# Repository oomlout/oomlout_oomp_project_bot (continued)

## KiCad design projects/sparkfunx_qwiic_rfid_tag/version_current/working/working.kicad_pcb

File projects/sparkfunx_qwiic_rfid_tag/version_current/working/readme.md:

# OOMP Project  
## Qwiic_RFID_Tag  by sparkfunX  
  
oomp key: oomp_projects_flat_sparkfunx_qwiic_rfid_tag  
(snippet of original readme)  
  
- SparkX ST25DV64KC Dynamic NFC/RFID Tag  
  
<p align="center">  
      
    <a href="https://twitter.com/intent/follow?screen_name=sparkfun">  
                    </a>  
</p>  
  
<table class="table table-hover table-striped table-bordered">  
    <tr align="center">  
     <td></td>  
    </tr>  
    <tr align="center">  
        <td><a href="https://www.sparkfun.com/products/19035">SparkFun Qwiic Dynamic RFID Tag - ST25DV64KC (SPX-19035)</a></td>  
    </tr>  
</table>  
  
The STMicroelectronics ST25DV _**dynamic**_ Near Frequency Communication / Radio Frequency Identification tag ICs are awesome! The ST25DV64KC offers 64-kBit (8-kBytes) of EEPROM memory which can be accessed over both I2C and RF (NFC)! It's a state-of-the-art tag which conforms to ISO/IEC 15693 or NFC Forum Type 5 recommendations. You can read and write the tag's memory using NFC even while the tag is powered down or disconnected!  
  
The EEPROM memory can be divided into four areas, each of which can have different levels of protection applied. Want to store your data so everyone has read and write acc  
  full source readme at [readme_src.md](readme_src.md)  
  
source repo at: [https://github.com/sparkfunX/Qwiic_RFID_Tag](https://github.com/sparkfunX/Qwiic_RFID_Tag)  
## Board  

## Schematic  

[schematic pdf](working_schematic.pdf)  
## Images

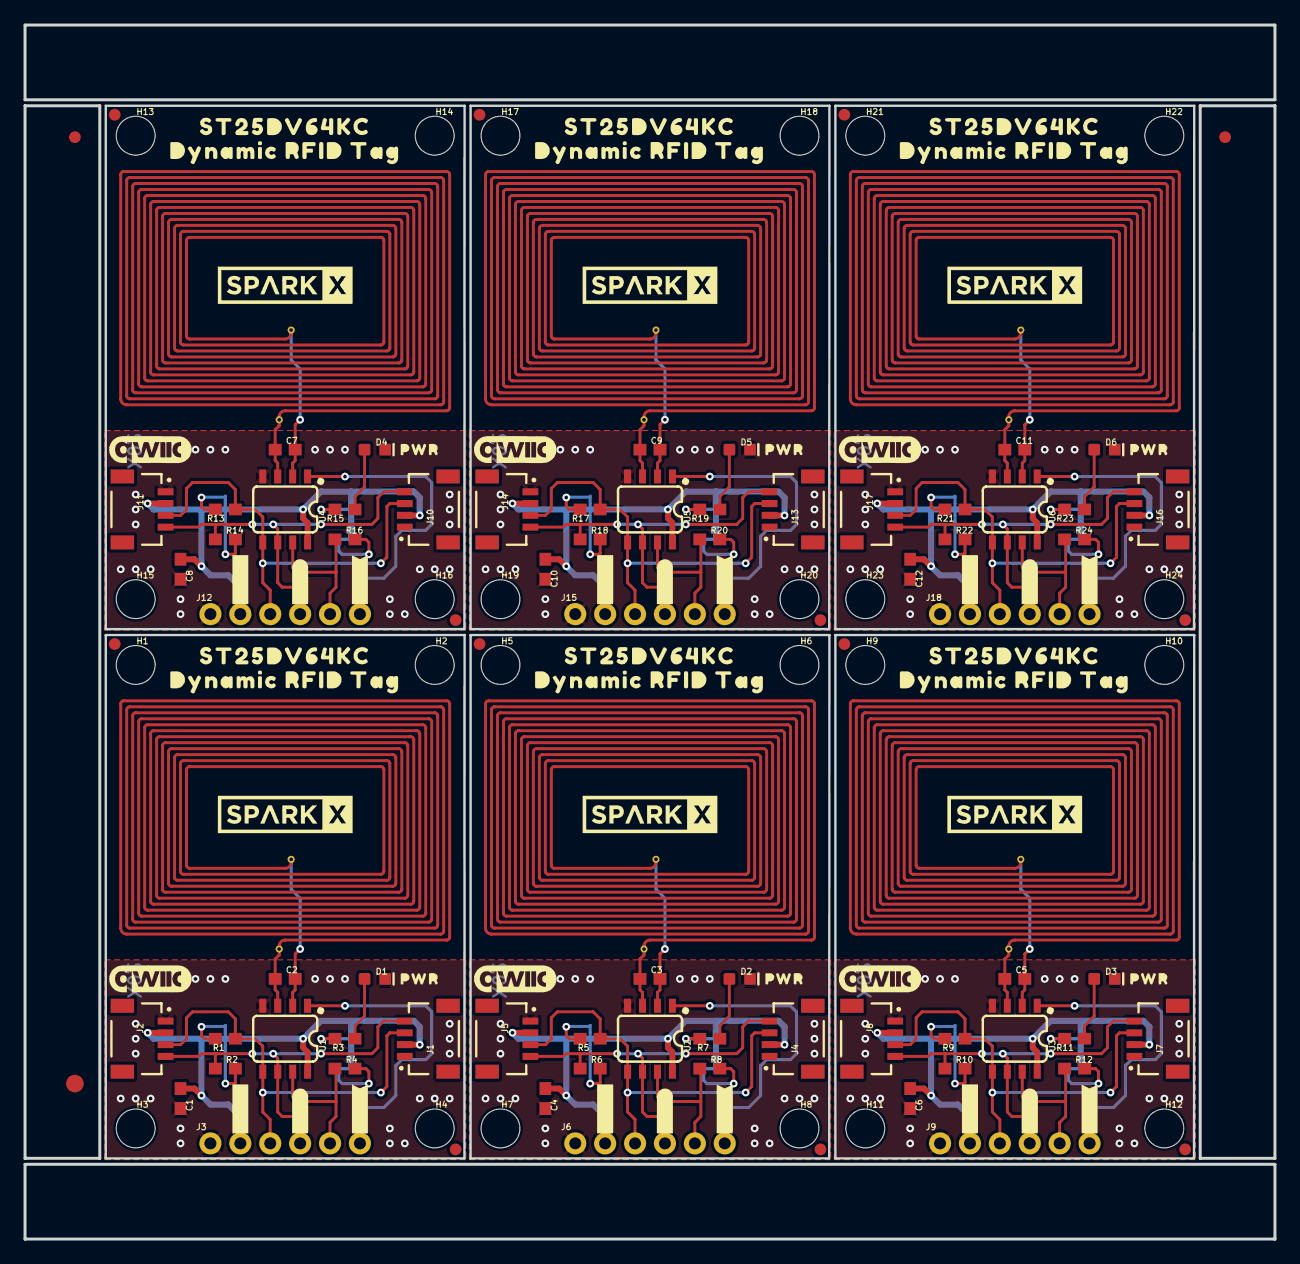
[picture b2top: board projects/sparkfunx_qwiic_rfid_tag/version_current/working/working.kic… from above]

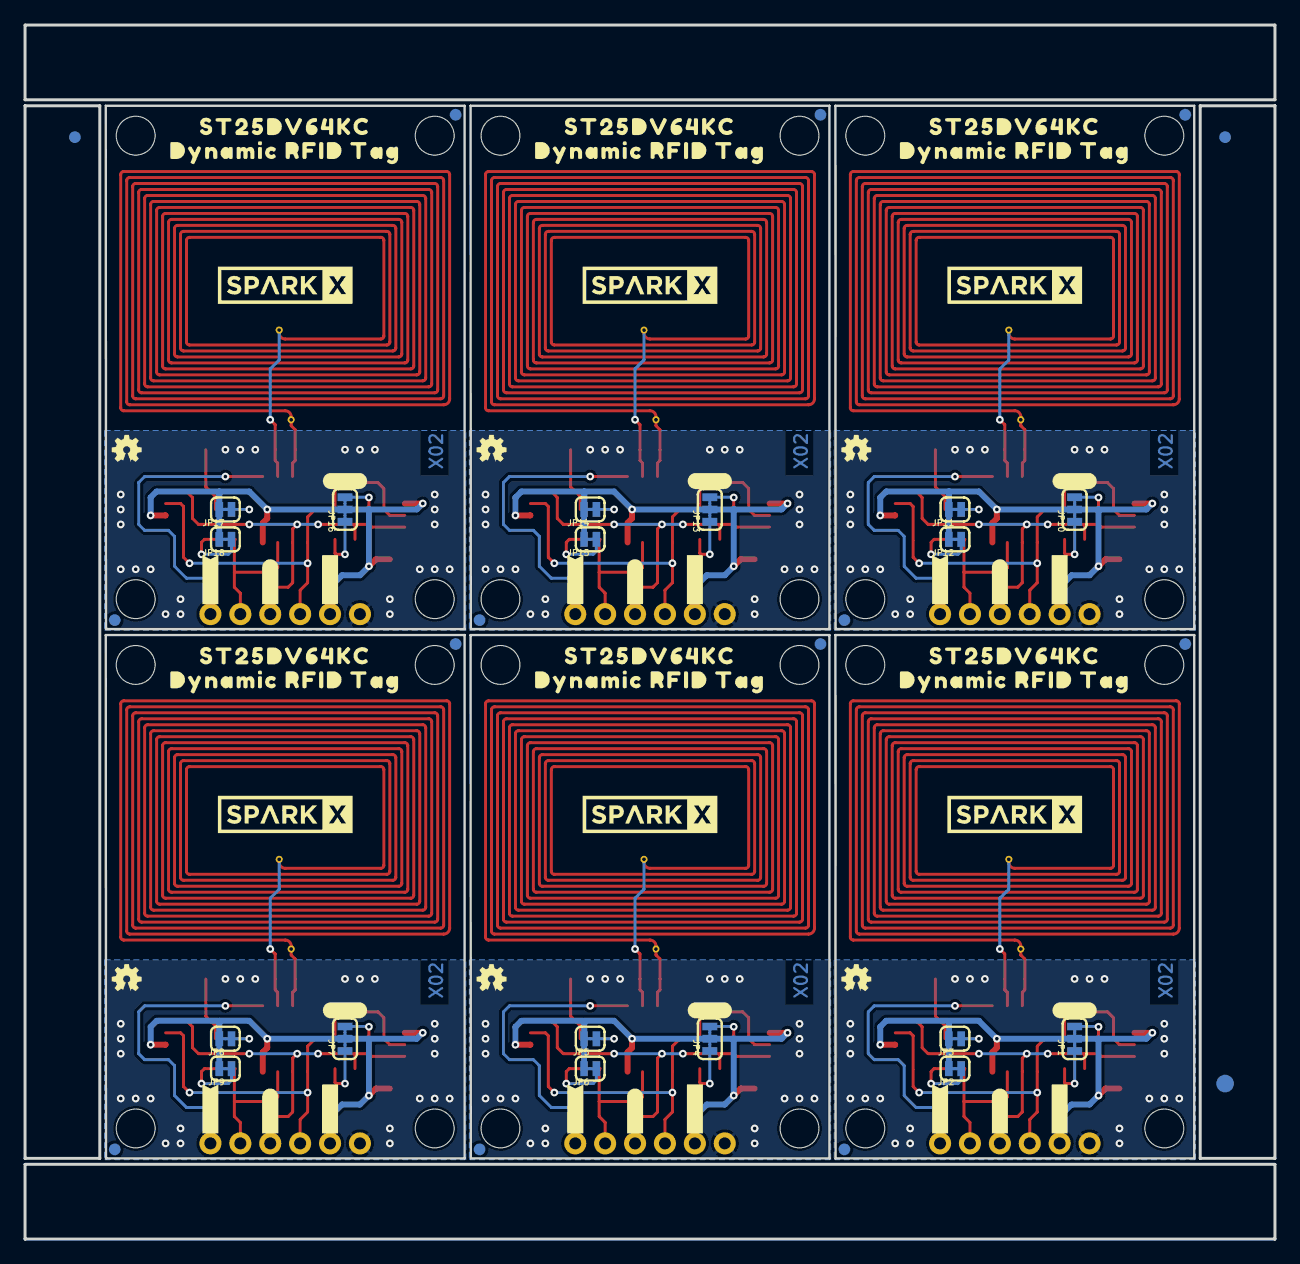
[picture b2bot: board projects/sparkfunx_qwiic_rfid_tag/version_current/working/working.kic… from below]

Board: 2 copper layers, 106.2 x 103.1 mm, 294 parts (111 on the bottom side), 78 nets.

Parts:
C1, C4, C6, C8, C10, C12: 0.1uF; 0603
C2, C3, C5, C7, C9, C11: 4.7pF; 0603
D1, D2, D3, D4, D5, D6: RED; LED-0603
E$1, E$2, E$3, E$4: FIDUCIAL-1X2
E$5, E$6: FIDUCIAL-1.5X3
FD1, FD2, FD3, FD4, FD5, FD6, FD7, FD8, FD9, FD10, FD11, FD12, FD13, FD14, FD15, FD16, FD17, FD18, FD19, FD20, FD21, FD22, FD23, FD24: FIDUCIAL1X2; FIDUCIAL-1X2
FRAME1, FRAME2, FRAME3, FRAME4, FRAME5, FRAME6: FRAME-LETTERNO_PACKAGE; DUMMY
H1, H2, H3, H4, H5, H6, H7, H8, H9, H10, H11, H12, H13, H14, H15, H16, H17, H18, H19, H20, H21, H22, H23, H24: STAND-OFF
J1, J2, J4, J5, J7, J8, J10, J11, J13, J14, J16, J17: Qwiic; JST04_1MM_RA
J3, J6, J9, J12, J15, J18: 1X06_NO_SILK
JP1, JP4, JP7, JP10, JP13, JP16: JUMPER-SMT_3_2-NC_TRACE_SILK; SMT-JUMPER_3_2-NC_TRACE_SILK
JP2, JP3, JP5, JP6, JP8, JP9, JP11, JP12, JP14, JP15, JP17, JP18: JUMPER-SMT_2_NC_TRACE_SILK; SMT-JUMPER_2_NC_TRACE_SILK
L1, L2, L3, L4, L5, L6: PCB_4UH_INDUCTOR
LOGO1, LOGO2, LOGO5, LOGO7, LOGO9, LOGO11: OSHW-LOGOMINI; OSHW-LOGO-MINI
LOGO3, LOGO4, LOGO6, LOGO8, LOGO10, LOGO12: QWIIC_LOGO_7MM; QWIIC_7MM
R1, R2, R5, R6, R9, R10, R13, R14, R17, R18, R21, R22: 2.2k; 0603
R3, R7, R11, R15, R19, R23: 1k; 0603
R4, R8, R12, R16, R20, R24: 10k; 0603
U1, U2, U3, U4, U5, U6: ST25DV64KC; SO08
U$1, U$2, U$12, U$14, U$45, U$46, U$67, U$68, U$89, U$90, U$111, U$112: SPARKX-LOGO5; SPARKX-LARGE
U$3, U$19, U$25, U$36, U$47, U$58, U$69, U$80, U$91, U$102, U$113, U$124: #3#3V#0
U$4, U$18, U$26, U$35, U$48, U$57, U$70, U$79, U$92, U$101, U$114, U$123: #GND#4
U$5, U$20, U$27, U$37, U$49, U$59, U$71, U$81, U$93, U$103, U$115, U$125: #SDA#5
U$6, U$21, U$28, U$38, U$50, U$60, U$72, U$82, U$94, U$104, U$116, U$126: #SCL#6
U$7, U$22, U$29, U$39, U$51, U$61, U$73, U$83, U$95, U$105, U$117, U$127: ##GPO##8
U$8, U$23, U$30, U$40, U$52, U$62, U$74, U$84, U$96, U$106, U$118, U$128: #VEH#7
U$9, U$31, U$53, U$75, U$97, U$119: PWR11
U$10, U$11, U$43, U$44, U$65, U$66, U$87, U$88, U$109, U$110, U$131, U$132: DYNAMIC_RFID_TAG0
U$13, U$24, U$41, U$42, U$63, U$64, U$85, U$86, U$107, U$108, U$129, U$130: ST25DV64KC5984
U$15, U$32, U$54, U$76, U$98, U$120: #I2C#11
U$16, U$33, U$55, U$77, U$99, U$121: ##GPO##9
U$17, U$34, U$56, U$78, U$100, U$122: #LED#10

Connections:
3.3V: C1.1, J1.2, J2.2, J3.2, JP1.2, JP2.2, JP3.2, U1.8
3.3V1: C4.1, J4.2, J5.2, J6.2, JP4.2, JP5.2, JP6.2, U2.8
3.3V2: C6.1, J7.2, J8.2, J9.2, JP7.2, JP8.2, JP9.2, U3.8
3.3V3: C8.1, J10.2, J11.2, J12.2, JP10.2, JP11.2, JP12.2, U4.8
3.3V4: C10.1, J13.2, J14.2, J15.2, JP13.2, JP14.2, JP15.2, U5.8
3.3V5: C12.1, J16.2, J17.2, J18.2, JP16.2, JP17.2, JP18.2, U6.8
AC0: C2.2, L1.IN1, U1.2
AC1: C2.1, L1.IN2, U1.3
AC2: C3.2, L2.IN1, U2.2
AC3: C3.1, L2.IN2, U2.3
AC4: C5.2, L3.IN1, U3.2
AC5: C5.1, L3.IN2, U3.3
AC6: C7.2, L4.IN1, U4.2
AC7: C7.1, L4.IN2, U4.3
AC8: C9.2, L5.IN1, U5.2
AC9: C9.1, L5.IN2, U5.3
AC10: C11.2, L6.IN1, U6.2
AC11: C11.1, L6.IN2, U6.3
GND: C1.2, D1.C, J1.1, J2.1, J3.1, U1.4
GND1: C4.2, D2.C, J4.1, J5.1, J6.1, U2.4
GND2: C6.2, D3.C, J7.1, J8.1, J9.1, U3.4
GND3: C8.2, D4.C, J10.1, J11.1, J12.1, U4.4
GND4: C10.2, D5.C, J13.1, J14.1, J15.1, U5.4
GND5: C12.2, D6.C, J16.1, J17.1, J18.1, U6.4
unnamed: JP3.1, R3.2
unnamed: JP1.3, R1.2
unnamed: JP1.1, R2.2
unnamed: D1.A, R3.1
unnamed: JP2.1, R4.2
unnamed: JP4.3, R5.2
unnamed: JP4.1, R6.2
unnamed: JP5.1, R7.2
unnamed: D2.A, R7.1
unnamed: JP6.1, R8.2
unnamed: JP7.3, R9.2
unnamed: JP7.1, R10.2
unnamed: JP8.1, R11.2
unnamed: D3.A, R11.1
unnamed: JP9.1, R12.2
unnamed: JP10.3, R13.2
unnamed: JP10.1, R14.2
unnamed: JP11.1, R15.2
unnamed: D4.A, R15.1
unnamed: JP12.1, R16.2
unnamed: JP13.3, R17.2
unnamed: JP13.1, R18.2
unnamed: JP14.1, R19.2
unnamed: D5.A, R19.1
unnamed: JP15.1, R20.2
unnamed: JP16.3, R21.2
unnamed: JP16.1, R22.2
unnamed: JP17.1, R23.2
unnamed: D6.A, R23.1
unnamed: JP18.1, R24.2
SCL: J1.4, J2.4, J3.4, R2.1, U1.6
SCL1: J4.4, J5.4, J6.4, R6.1, U2.6
SCL2: J7.4, J8.4, J9.4, R10.1, U3.6
SCL3: J10.4, J11.4, J12.4, R14.1, U4.6
SCL4: J13.4, J14.4, J15.4, R18.1, U5.6
SCL5: J16.4, J17.4, J18.4, R22.1, U6.6
SDA: J1.3, J2.3, J3.3, R1.1, U1.5
SDA1: J4.3, J5.3, J6.3, R5.1, U2.5
SDA2: J7.3, J8.3, J9.3, R9.1, U3.5
SDA3: J10.3, J11.3, J12.3, R13.1, U4.5
SDA4: J13.3, J14.3, J15.3, R17.1, U5.5
SDA5: J16.3, J17.3, J18.3, R21.1, U6.5
VEH: J3.6, U1.1
VEH1: J6.6, U2.1
VEH2: J9.6, U3.1
VEH3: J12.6, U4.1
VEH4: J15.6, U5.1
VEH5: J18.6, U6.1
~GPO: J3.5, R4.1, U1.7
~GPO1: J6.5, R8.1, U2.7
~GPO2: J9.5, R12.1, U3.7
~GPO3: J12.5, R16.1, U4.7
~GPO4: J15.5, R20.1, U5.7
~GPO5: J18.5, R24.1, U6.7

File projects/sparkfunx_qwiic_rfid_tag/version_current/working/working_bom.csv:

"Id";"Designator";"Footprint";"Quantity";"Designation";"Supplier and ref";
1;"U$71,U$115,U$49,U$5,U$93,U$27,U$103,U$37,U$20,U$125,U$59,U$81";"#SDA#5";12;"";;;
2;"R19,R7,R3,R15,R23,R11";"0603";6;"1k";;;
3;"FD2,FD20,FD10,FD6,FD16,FD22,FD4,FD12,FD24,FD18,FD8,FD14,FD7,FD23,FD11,FD19,FD5,FD15,FD3,FD17,FD21,FD1,FD9,FD13";"FIDUCIAL-1X2";24;"FIDUCIAL1X2";;;
4;"R2,R6,R14,R13,R5,R21,R22,R10,R1,R9,R18,R17";"0603";12;"2.2k";;;
5;"U$116,U$94,U$6,U$72,U$28,U$50,U$21,U$104,U$60,U$126,U$38,U$82";"#SCL#6";12;"";;;
6;"U$4,U$114,U$26,U$70,U$92,U$48,U$101,U$79,U$57,U$35,U$18,U$123";"#GND#4";12;"";;;
7;"U$12,U$89,U$111,U$45,U$1,U$67,U$2,U$68,U$90,U$14,U$46,U$112";"SPARKX-LARGE";12;"SPARKX-LOGO5";;;
8;"LOGO6,LOGO8,LOGO4,LOGO3,LOGO12,LOGO10";"QWIIC_7MM";6;"QWIIC_LOGO_7MM";;;
9;"U$131,U$87,U$10,U$43,U$109,U$65,U$66,U$132,U$110,U$88,U$11,U$44";"DYNAMIC_RFID_TAG0";12;"";;;
10;"U$30,U$96,U$74,U$8,U$118,U$52,U$106,U$62,U$23,U$40,U$84,U$128";"#VEH#7";12;"";;;
11;"U$9,U$119,U$97,U$31,U$53,U$75";"PWR11";6;"";;;
12;"D6,D2,D3,D1,D4,D5";"LED-0603";6;"RED";;;
13;"H5,H24,H12,H19,H16,H21,H8,H3,H7,H9,H22,H4,H15,H2,H14,H13,H17,H20,H23,H6,H11,H18,H1,H10";"STAND-OFF";24;"STAND-OFF";;;
14;"J9,J6,J12,J3,J18,J15";"1X06_NO_SILK";6;"";;;
15;"FRAME6,FRAME3,FRAME2,FRAME1,FRAME4,FRAME5";"DUMMY";6;"FRAME-LETTERNO_PACKAGE";;;
16;"E$3,E$1,E$2,E$4";"FIDUCIAL-1X2";4;"";;;
17;"C6,C12,C8,C10,C1,C4";"0603";6;"0.1uF";;;
18;"L1,L6,L2,L3,L4,L5";"PCB_4UH_INDUCTOR";6;"PCB_4UH_INDUCTOR";;;
19;"J11,J1,J14,J2,J17,J8,J7,J4,J10,J16,J5,J13";"JST04_1MM_RA";12;"Qwiic";;;
20;"U$63,U$41,U$107,U$13,U$85,U$129,U$130,U$24,U$64,U$86,U$42,U$108";"ST25DV64KC5984";12;"";;;
21;"U1,U6,U2,U4,U3,U5";"SO08";6;"ST25DV64KC";;;
22;"U$117,U$95,U$73,U$51,U$7,U$29,U$127,U$39,U$22,U$61,U$83,U$105";"##GPO##8";12;"";;;
23;"U$25,U$113,U$47,U$3,U$91,U$69,U$58,U$80,U$102,U$36,U$124,U$19";"#3#3V#0";12;"";;;
24;"R12,R8,R16,R20,R24,R4";"0603";6;"10k";;;
25;"C7,C11,C9,C3,C5,C2";"0603";6;"4.7pF";;;
26;"E$5,E$6";"FIDUCIAL-1.5X3";2;"";;;
27;"JP15,JP8,JP5,JP12,JP11,JP18,JP3,JP9,JP17,JP2,JP6,JP14";"SMT-JUMPER_2_NC_TRACE_SILK";12;"JUMPER-SMT_2_NC_TRACE_SILK";;;
28;"LOGO1,LOGO9,LOGO7,LOGO2,LOGO11,LOGO5";"OSHW-LOGO-MINI";6;"OSHW-LOGOMINI";;;
29;"U$100,U$17,U$34,U$122,U$78,U$56";"#LED#10";6;"";;;
30;"U$55,U$16,U$121,U$77,U$33,U$99";"##GPO##9";6;"";;;
31;"U$54,U$76,U$120,U$98,U$32,U$15";"#I2C#11";6;"";;;
32;"JP4,JP16,JP13,JP1,JP10,JP7";"SMT-JUMPER_3_2-NC_TRACE_SILK";6;"JUMPER-SMT_3_2-NC_TRACE_SILK";;;

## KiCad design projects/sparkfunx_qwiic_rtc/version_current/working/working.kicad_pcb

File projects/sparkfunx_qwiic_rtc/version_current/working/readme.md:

# Qwiic_RTC by sparkfunX  
This is a harvested standardized copy of a project from github.  
The original project can be found at:  
https://github.com/sparkfunX/Qwiic_RTC  
Please consult that link for additional, details, files, and license information.  
Note: It was auto harvested and if the original repo had more than one board file or anything out of the ordinary the files here are likely not representative.

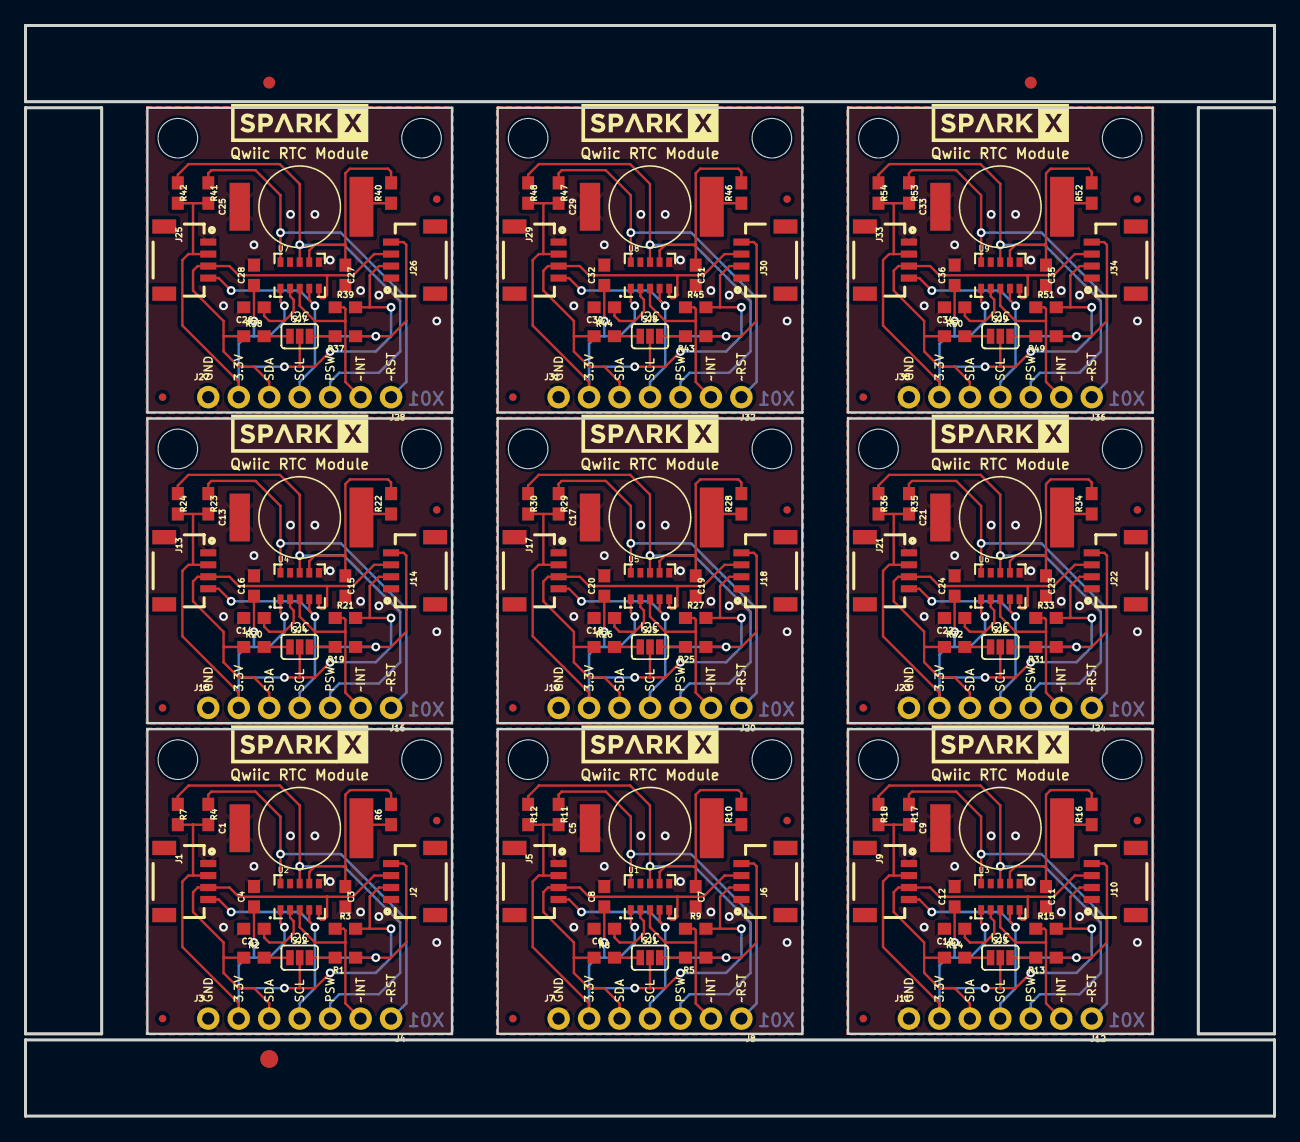
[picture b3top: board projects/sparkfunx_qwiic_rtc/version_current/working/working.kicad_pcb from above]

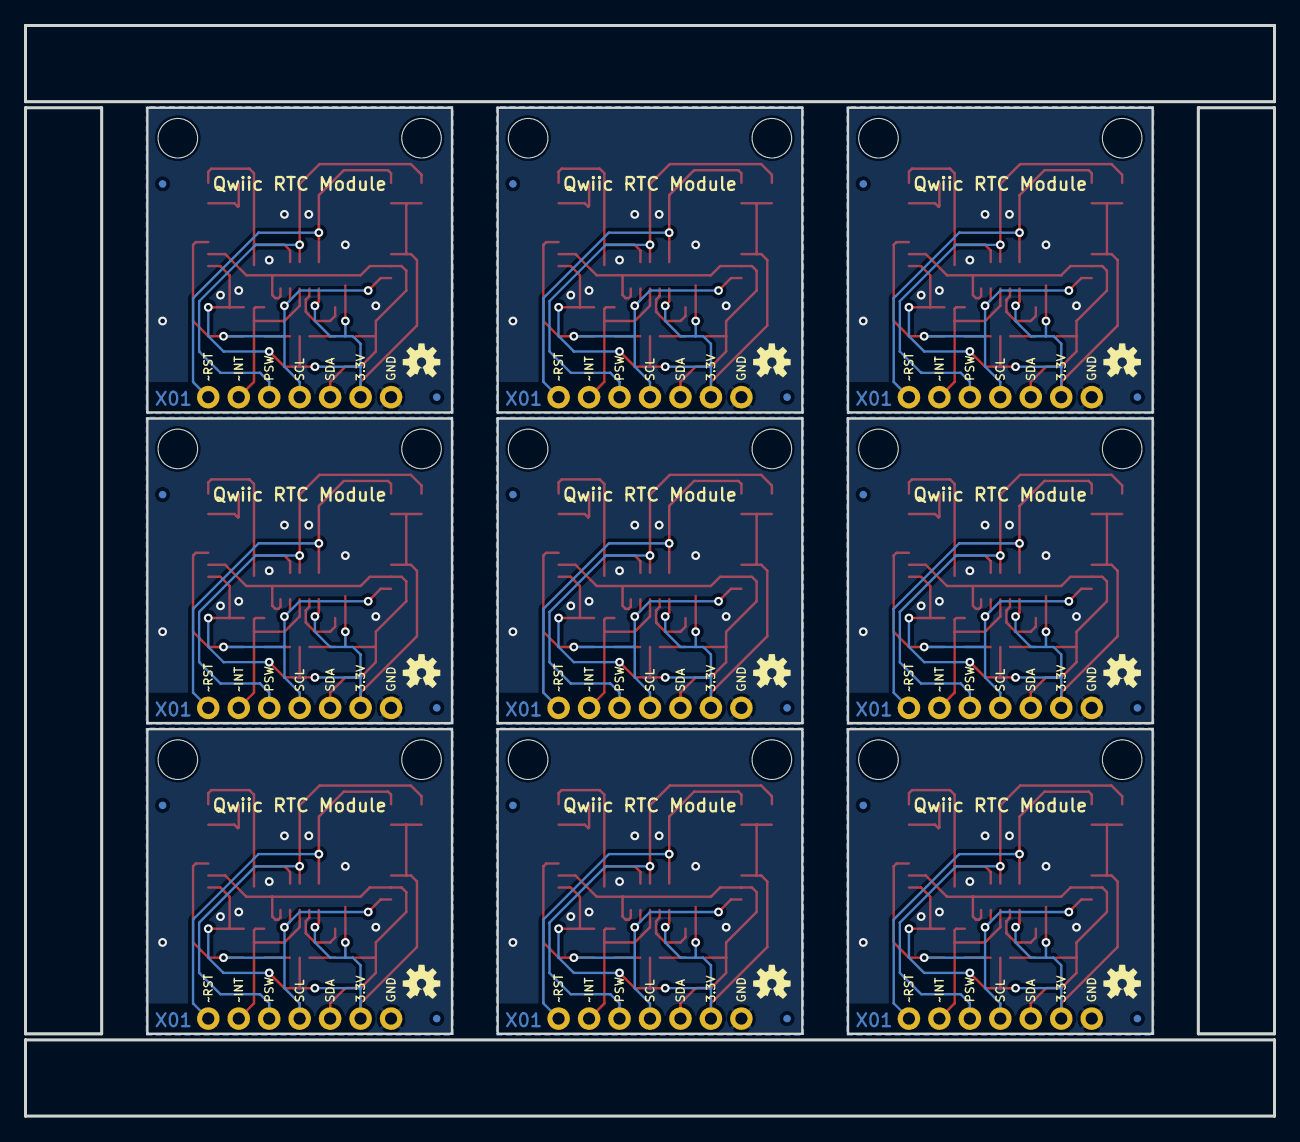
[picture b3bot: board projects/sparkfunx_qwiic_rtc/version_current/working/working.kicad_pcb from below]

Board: 2 copper layers, 104.1 x 90.9 mm, 219 parts (27 on the bottom side), 108 nets.

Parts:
C1, C5, C9, C13, C17, C21, C25, C29, C33: .22F-SUPERCAP; DSK-RADIAL-6.8MM
C2, C6, C10, C14, C18, C22, C26, C30, C34: 47pF; 0603
C3, C4, C7, C8, C11, C12, C15, C16, C19, C20, C23, C24, C27, C28, C31, C32, C35, C36: 10nF; 0603
E$1, E$2: FIDUCIAL-1X2
E$3: FIDUCIAL-1.5X3
FD1, FD2, FD3, FD4, FD5, FD6, FD7, FD8, FD9, FD10, FD11, FD12, FD13, FD14, FD15, FD16, FD17, FD18, FD19, FD20, FD21, FD22, FD23, FD24, FD25, FD26, FD27, FD28, FD29, FD30, FD31, FD32, FD33, FD34, FD35, FD36: FIDUCIALUFIDUCIAL; FIDUCIAL-MICRO
J1, J2, J5, J6, J9, J10, J13, J14, J17, J18, J21, J22, J25, J26, J29, J30, J33, J34: SMD; 1X04_1MM_RA
J3, J7, J11, J15, J19, J23, J27, J31, J35: PTH; 1X04_NO_SILK
J4, J8, J12, J16, J20, J24, J28, J32, J36: 1X03_NO_SILK
LOGO1, LOGO2, LOGO3, LOGO4, LOGO5, LOGO6, LOGO7, LOGO8, LOGO9: OSHW-LOGOS; OSHW-LOGO-S
R1, R2, R5, R8, R13, R14, R19, R20, R25, R26, R31, R32, R37, R38, R43, R44, R49, R50: 2.2k; 0603
R3, R4, R7, R9, R11, R12, R15, R17, R18, R21, R23, R24, R27, R29, R30, R33, R35, R36, R39, R41, R42, R45, R47, R48, R51, R53, R54: 10k; 0603
R6, R10, R16, R22, R28, R34, R40, R46, R52: 1K; 0603
SJ1, SJ2, SJ3, SJ4, SJ5, SJ6, SJ7, SJ8, SJ9: JUMPER-SMT_3_2-NC_PASTE_SILK; SMT-JUMPER_3_2-NC_PASTE_SILK
U1, U2, U3, U4, U5, U6, U7, U8, U9: RV-1805
U$1, U$4, U$9, U$12, U$15, U$18, U$21, U$24, U$27: SPARKX-LOGO5; SPARKX-LARGE
U$2, U$3, U$5, U$6, U$7, U$8, U$10, U$11, U$13, U$14, U$16, U$17, U$19, U$20, U$22, U$23, U$25, U$26: STAND-OFF

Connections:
3.3V: C4.1, J1.2, J2.2, J3.2, R3.2, R4.2, R7.2, SJ2.2, U2.1
3.3V1: C8.1, J5.2, J6.2, J7.2, R9.2, R11.2, R12.2, SJ1.2, U1.1
3.3V2: C12.1, J9.2, J10.2, J11.2, R15.2, R17.2, R18.2, SJ3.2, U3.1
3.3V3: C16.1, J13.2, J14.2, J15.2, R21.2, R23.2, R24.2, SJ4.2, U4.1
3.3V4: C20.1, J17.2, J18.2, J19.2, R27.2, R29.2, R30.2, SJ5.2, U5.1
3.3V5: C24.1, J21.2, J22.2, J23.2, R33.2, R35.2, R36.2, SJ6.2, U6.1
3.3V6: C28.1, J25.2, J26.2, J27.2, R39.2, R41.2, R42.2, SJ7.2, U7.1
3.3V7: C32.1, J29.2, J30.2, J31.2, R45.2, R47.2, R48.2, SJ8.2, U8.1
3.3V8: C36.1, J33.2, J34.2, J35.2, R51.2, R53.2, R54.2, SJ9.2, U9.1
GND: C1.-, C2.2, C3.2, C4.2, J1.1, J2.1, J3.1, U2.6, U2.9
GND1: C5.-, C6.2, C7.2, C8.2, J5.1, J6.1, J7.1, U1.6, U1.9
GND2: C9.-, C10.2, C11.2, C12.2, J9.1, J10.1, J11.1, U3.6, U3.9
GND3: C13.-, C14.2, C15.2, C16.2, J13.1, J14.1, J15.1, U4.6, U4.9
GND4: C17.-, C18.2, C19.2, C20.2, J17.1, J18.1, J19.1, U5.6, U5.9
GND5: C21.-, C22.2, C23.2, C24.2, J21.1, J22.1, J23.1, U6.6, U6.9
GND6: C25.-, C26.2, C27.2, C28.2, J25.1, J26.1, J27.1, U7.6, U7.9
GND7: C29.-, C30.2, C31.2, C32.2, J29.1, J30.1, J31.1, U8.6, U8.9
GND8: C33.-, C34.2, C35.2, C36.2, J33.1, J34.1, J35.1, U9.6, U9.9
unnamed: R1.2, SJ2.3
unnamed: R2.2, SJ2.1
unnamed: R5.2, SJ1.3
unnamed: C2.1, U2.2
unnamed: C1.+, R6.1
unnamed: R8.2, SJ1.1
unnamed: C6.1, U1.2
unnamed: C5.+, R10.1
unnamed: R13.2, SJ3.3
unnamed: R14.2, SJ3.1
unnamed: C10.1, U3.2
unnamed: C9.+, R16.1
unnamed: R19.2, SJ4.3
unnamed: R20.2, SJ4.1
unnamed: C14.1, U4.2
unnamed: C13.+, R22.1
unnamed: R25.2, SJ5.3
unnamed: R26.2, SJ5.1
unnamed: C18.1, U5.2
unnamed: C17.+, R28.1
unnamed: R31.2, SJ6.3
unnamed: R32.2, SJ6.1
unnamed: C22.1, U6.2
unnamed: C21.+, R34.1
unnamed: R37.2, SJ7.3
unnamed: R38.2, SJ7.1
unnamed: C26.1, U7.2
unnamed: C25.+, R40.1
unnamed: R43.2, SJ8.3
unnamed: R44.2, SJ8.1
unnamed: C30.1, U8.2
unnamed: C29.+, R46.1
unnamed: R49.2, SJ9.3
unnamed: R50.2, SJ9.1
unnamed: C34.1, U9.2
unnamed: C33.+, R52.1
PSW: J4.3, R7.1, U2.8
PSW1: J8.3, R12.1, U1.8
PSW2: J12.3, R18.1, U3.8
PSW3: J16.3, R24.1, U4.8
PSW4: J20.3, R30.1, U5.8
PSW5: J24.3, R36.1, U6.8
PSW6: J28.3, R42.1, U7.8
PSW7: J32.3, R48.1, U8.8
PSW8: J36.3, R54.1, U9.8
SCL: J1.4, J2.4, J3.4, R1.1, U2.4
SCL1: J5.4, J6.4, J7.4, R5.1, U1.4
SCL2: J9.4, J10.4, J11.4, R13.1, U3.4
SCL3: J13.4, J14.4, J15.4, R19.1, U4.4
SCL4: J17.4, J18.4, J19.4, R25.1, U5.4
SCL5: J21.4, J22.4, J23.4, R31.1, U6.4
SCL6: J25.4, J26.4, J27.4, R37.1, U7.4
SCL7: J29.4, J30.4, J31.4, R43.1, U8.4
SCL8: J33.4, J34.4, J35.4, R49.1, U9.4
SDA: J1.3, J2.3, J3.3, R2.1, U2.5
SDA1: J5.3, J6.3, J7.3, R8.1, U1.5
SDA2: J9.3, J10.3, J11.3, R14.1, U3.5
SDA3: J13.3, J14.3, J15.3, R20.1, U4.5
SDA4: J17.3, J18.3, J19.3, R26.1, U5.5
SDA5: J21.3, J22.3, J23.3, R32.1, U6.5
SDA6: J25.3, J26.3, J27.3, R38.1, U7.5
SDA7: J29.3, J30.3, J31.3, R44.1, U8.5
SDA8: J33.3, J34.3, J35.3, R50.1, U9.5
VBACKUP: C3.1, R6.2, U2.7
VBACKUP1: C7.1, R10.2, U1.7
VBACKUP2: C11.1, R16.2, U3.7
VBACKUP3: C15.1, R22.2, U4.7
VBACKUP4: C19.1, R28.2, U5.7
VBACKUP5: C23.1, R34.2, U6.7
VBACKUP6: C27.1, R40.2, U7.7
VBACKUP7: C31.1, R46.2, U8.7
VBACKUP8: C35.1, R52.2, U9.7
~INT1: J8.2, R9.1, U1.3
~INT2: J12.2, R15.1, U3.3
~INT3: J16.2, R21.1, U4.3
~INT4: J20.2, R27.1, U5.3
~INT5: J24.2, R33.1, U6.3
~INT6: J28.2, R39.1, U7.3
~INT7: J32.2, R45.1, U8.3
~INT8: J36.2, R51.1, U9.3
~INT: J4.2, R3.1, U2.3
~RST1: J8.1, R11.1, U1.10
~RST2: J12.1, R17.1, U3.10
~RST3: J16.1, R23.1, U4.10
~RST4: J20.1, R29.1, U5.10
~RST5: J24.1, R35.1, U6.10
~RST6: J28.1, R41.1, U7.10
~RST7: J32.1, R47.1, U8.10
~RST8: J36.1, R53.1, U9.10
~RST: J4.1, R4.1, U2.10

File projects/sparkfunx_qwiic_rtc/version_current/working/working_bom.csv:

"Id";"Designator";"Footprint";"Quantity";"Designation";"Supplier and ref";
1;"R25,R5,R20,R49,R44,R50,R43,R31,R38,R19,R14,R2,R37,R13,R1,R26,R8,R32";"0603";18;"2.2k";;;
2;"U$12,U$9,U$24,U$15,U$18,U$1,U$21,U$4,U$27";"SPARKX-LARGE";9;"SPARKX-LOGO5";;;
3;"J22,J9,J17,J2,J18,J6,J10,J29,J14,J34,J5,J1,J30,J26,J25,J33,J13,J21";"1X04_1MM_RA";18;"SMD";;;
4;"J36,J4,J12,J20,J16,J28,J32,J24,J8";"1X03_NO_SILK";9;"";;;
5;"U$7,U$13,U$17,U$8,U$19,U$3,U$11,U$23,U$16,U$22,U$14,U$10,U$6,U$2,U$25,U$20,U$26,U$5";"STAND-OFF";18;"STAND-OFF";;;
6;"FD34,FD10,FD30,FD32,FD18,FD8,FD26,FD20,FD6,FD14,FD28,FD4,FD16,FD12,FD22,FD2,FD36,FD24,FD33,FD13,FD5,FD7,FD27,FD23,FD1,FD29,FD21,FD35,FD9,FD31,FD17,FD15,FD3,FD11,FD25,FD19";"FIDUCIAL-MICRO";36;"FIDUCIALUFIDUCIAL";;;
7;"C36,C7,C16,C3,C23,C32,C12,C11,C24,C8,C4,C19,C31,C27,C15,C20,C35,C28";"0603";18;"10nF";;;
8;"R42,R12,R4,R48,R11,R23,R9,R24,R51,R7,R33,R30,R47,R18,R45,R39,R29,R41,R27,R15,R17,R54,R21,R3,R53,R35,R36";"0603";27;"10k";;;
9;"J7,J11,J35,J23,J27,J19,J31,J3,J15";"1X04_NO_SILK";9;"PTH";;;
10;"SJ5,SJ6,SJ1,SJ7,SJ3,SJ8,SJ2,SJ4,SJ9";"SMT-JUMPER_3_2-NC_PASTE_SILK";9;"JUMPER-SMT_3_2-NC_PASTE_SILK";;;
11;"R6,R28,R16,R34,R22,R10,R46,R40,R52";"0603";9;"1K";;;
12;"C17,C21,C33,C9,C5,C1,C25,C13,C29";"DSK-RADIAL-6.8MM";9;".22F-SUPERCAP";;;
13;"U1,U5,U8,U4,U9,U6,U2,U7,U3";"RV-1805";9;"RV-1805";;;
14;"C10,C22,C14,C18,C2,C30,C26,C34,C6";"0603";9;"47pF";;;
15;"E$2,E$1";"FIDUCIAL-1X2";2;"";;;
16;"E$3";"FIDUCIAL-1.5X3";1;"";;;
17;"LOGO4,LOGO6,LOGO2,LOGO9,LOGO3,LOGO1,LOGO8,LOGO7,LOGO5";"OSHW-LOGO-S";9;"OSHW-LOGOS";;;

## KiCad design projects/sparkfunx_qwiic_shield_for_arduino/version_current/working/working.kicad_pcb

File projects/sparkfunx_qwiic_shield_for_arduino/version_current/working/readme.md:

# Qwiic_Shield_for_Arduino by sparkfunX  
This is a harvested standardized copy of a project from github.  
The original project can be found at:  
https://github.com/sparkfunX/Qwiic_Shield_for_Arduino  
Please consult that link for additional, details, files, and license information.  
Note: It was auto harvested and if the original repo had more than one board file or anything out of the ordinary the files here are likely not representative.

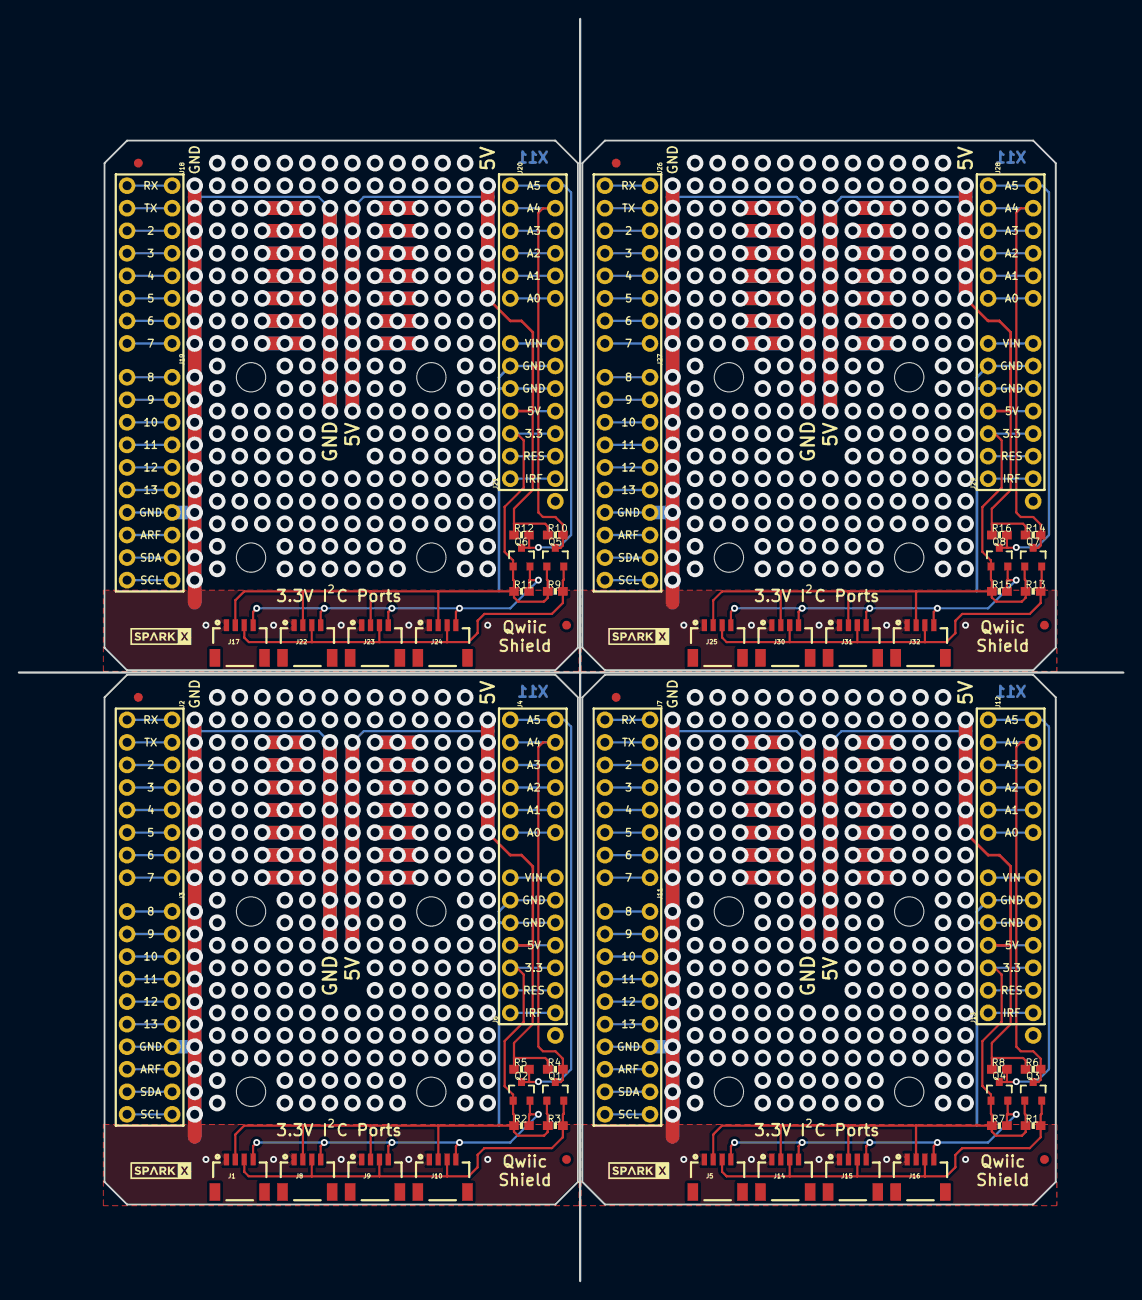
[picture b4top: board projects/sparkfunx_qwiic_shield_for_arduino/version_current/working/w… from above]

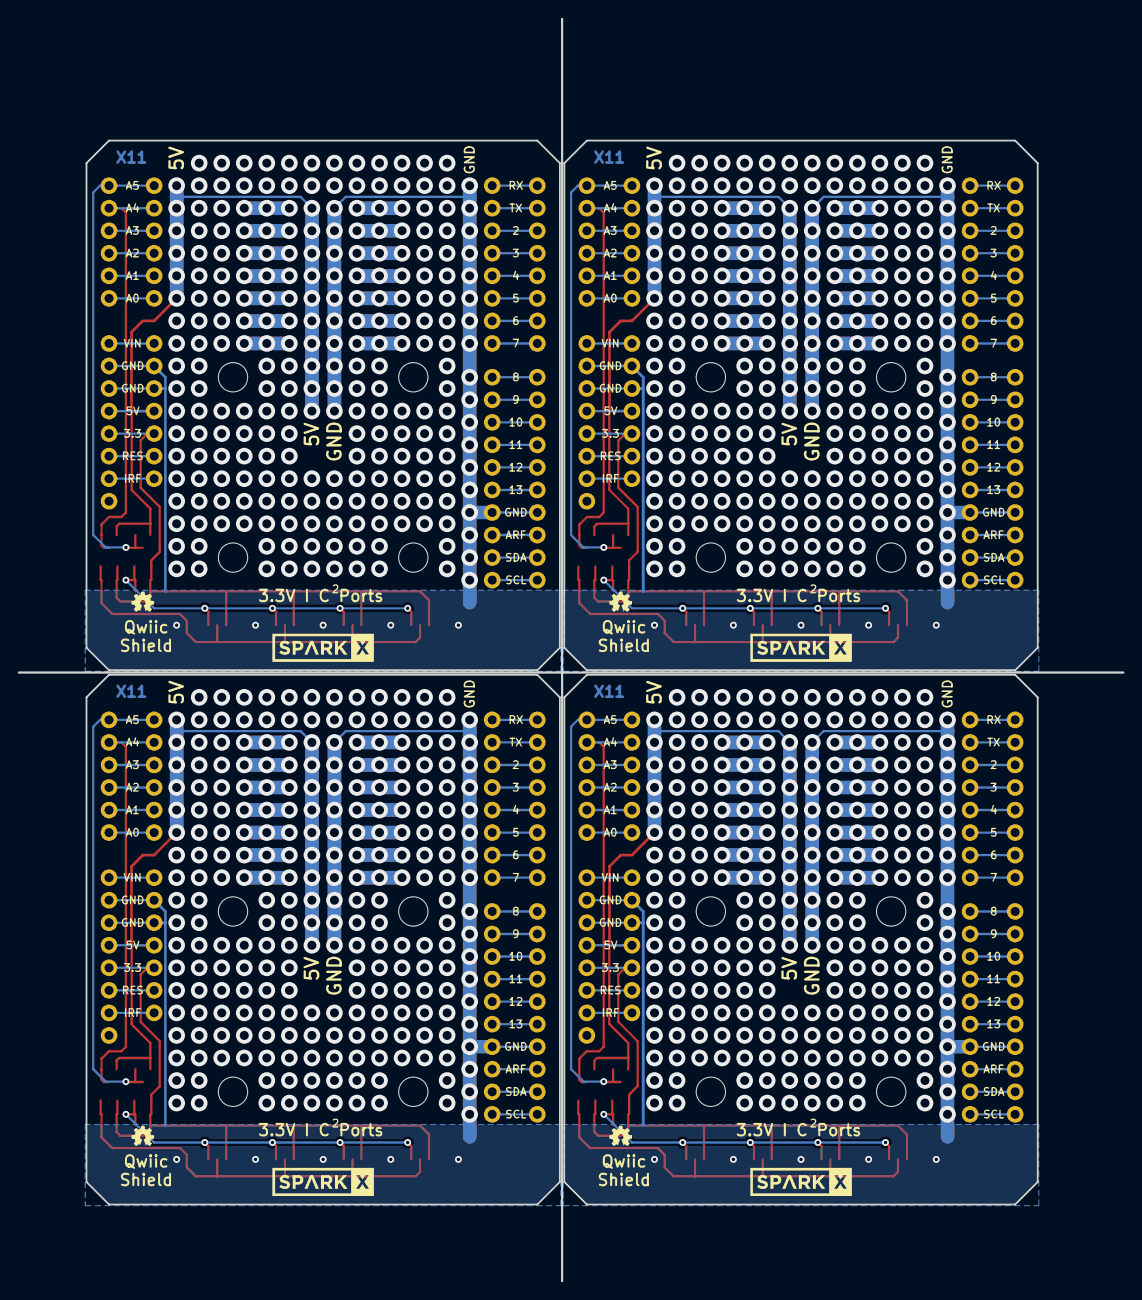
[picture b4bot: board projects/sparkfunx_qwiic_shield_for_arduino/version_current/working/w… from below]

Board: 2 copper layers, 124.5 x 142.2 mm, 84 parts (8 on the bottom side), 124 nets.

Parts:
FD1, FD2, FD3, FD4, FD5, FD6, FD7, FD8: FIDUCIAL1X2; FIDUCIAL-1X2
J1, J5, J8, J9, J10, J14, J15, J16, J17, J22, J23, J24, J25, J30, J31, J32: 1X04_1MM_RA
J2, J7, J18, J26: 1X08_NO_SILK
J3, J11, J19, J27: 1X10_NO_SILK
J4, J12, J20, J28: 1X06_NO_SILK
J6, J13, J21, J29: 1X07_NO_SILK
LOGO1, LOGO2, LOGO3, LOGO4: OSHW-LOGOMINI; OSHW-LOGO-MINI
Q1, Q2, Q3, Q4, Q5, Q6, Q7, Q8: 200mA/50V; SOT23-3
R1, R2, R3, R4, R5, R6, R7, R8, R9, R10, R11, R12, R13, R14, R15, R16: 4.7K; 0603-RES
U1, U2, U3, U4: ARDUINO UNO; UNO_R3_SHIELD_NOLABELS
U$1, U$4, U$7, U$10: SPARKX-LOGO3; SPARKX-SMALL
U$2, U$5, U$8, U$11: SPARKX-LOGO5; SPARKX-LARGE
U$3, U$6, U$9, U$12: QWIIC_BOARD_OUTLINEH; QWIIC_BOARD_MOUNT_HOLES

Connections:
3.3V: J1.2, J6.3, J8.2, J9.2, J10.2, Q1.1, Q2.1, R2.1, R3.1, U1.3.3V
3.3V1: J5.2, J13.3, J14.2, J15.2, J16.2, Q3.1, Q4.1, R1.1, R7.1, U2.3.3V
3.3V2: J17.2, J21.3, J22.2, J23.2, J24.2, Q5.1, Q6.1, R9.1, R11.1, U3.3.3V
3.3V3: J25.2, J29.3, J30.2, J31.2, J32.2, Q7.1, Q8.1, R13.1, R15.1, U4.3.3V
5V: J6.4, R4.1, R5.1, U1.5V
5V1: J13.4, R6.1, R8.1, U2.5V
5V2: J21.4, R10.1, R12.1, U3.5V
5V3: J29.4, R14.1, R16.1, U4.5V
A0: J4.6, U1.A0
A1: J4.5, U1.A1
A2: J4.4, U1.A2
A3: J4.3, U1.A3
A4: J12.3, U2.A3
A5: J12.4, U2.A2
A6: J12.5, U2.A1
A7: J12.6, U2.A0
A8: J20.3, U3.A3
A9: J20.4, U3.A2
A10: J20.5, U3.A1
A11: J20.6, U3.A0
A12: J28.3, U4.A3
A13: J28.4, U4.A2
A14: J28.5, U4.A1
A15: J28.6, U4.A0
AREF: J3.8, U1.AREF
AREF1: J11.8, U2.AREF
AREF2: J19.8, U3.AREF
AREF3: J27.8, U4.AREF
D1: J7.3, U2.D2
D2: J2.3, U1.D2
D3: J2.4, U1.D3
D4: J2.5, U1.D4
D5: J2.6, U1.D5
D6: J2.7, U1.D6
D7: J2.8, U1.D7
D8: J3.1, U1.D8
D9: J3.2, U1.D9
D10: J3.3, U1.D10
D11: J3.4, U1.D11
D12: J3.5, U1.D12
D13: J3.6, U1.D13
D14: J7.4, U2.D3
D15: J7.5, U2.D4
D16: J7.6, U2.D5
D17: J7.7, U2.D6
D18: J7.8, U2.D7
D19: J11.1, U2.D8
D20: J11.2, U2.D9
D21: J11.3, U2.D10
D22: J11.4, U2.D11
D23: J11.5, U2.D12
D24: J11.6, U2.D13
D25: J18.3, U3.D2
D26: J18.4, U3.D3
D27: J18.5, U3.D4
D28: J18.6, U3.D5
D29: J18.7, U3.D6
D30: J18.8, U3.D7
D31: J19.1, U3.D8
D32: J19.2, U3.D9
D33: J19.3, U3.D10
D34: J19.4, U3.D11
D35: J19.5, U3.D12
D36: J19.6, U3.D13
D37: J26.3, U4.D2
D38: J26.4, U4.D3
D39: J26.5, U4.D4
D40: J26.6, U4.D5
D41: J26.7, U4.D6
D42: J26.8, U4.D7
D43: J27.1, U4.D8
D44: J27.2, U4.D9
D45: J27.3, U4.D10
D46: J27.4, U4.D11
D47: J27.5, U4.D12
D48: J27.6, U4.D13
GND: J1.1, J3.7, J6.5, J6.6, J8.1, J9.1, J10.1, U1.GND@0, U1.GND@1, U1.GND@2
GND1: J5.1, J11.7, J13.5, J13.6, J14.1, J15.1, J16.1, U2.GND@0, U2.GND@1, U2.GND@2
GND2: J17.1, J19.7, J21.5, J21.6, J22.1, J23.1, J24.1, U3.GND@0, U3.GND@1, U3.GND@2
GND3: J25.1, J27.7, J29.5, J29.6, J30.1, J31.1, J32.1, U4.GND@0, U4.GND@1, U4.GND@2
HV_SCL: J4.1, Q2.3, R5.2, U1.A5
HV_SCL1: J12.1, Q4.3, R8.2, U2.A5
HV_SCL2: J20.1, Q6.3, R12.2, U3.A5
HV_SCL3: J28.1, Q8.3, R16.2, U4.A5
HV_SDA: J4.2, Q1.3, R4.2, U1.A4
HV_SDA1: J12.2, Q3.3, R6.2, U2.A4
HV_SDA2: J20.2, Q5.3, R10.2, U3.A4
HV_SDA3: J28.2, Q7.3, R14.2, U4.A4
IOREF: J6.1, U1.IOREF
IOREF1: J13.1, U2.IOREF
IOREF2: J21.1, U3.IOREF
IOREF3: J29.1, U4.IOREF
RES: J6.2, U1.RES
RES1: J13.2, U2.RES
RES2: J21.2, U3.RES
RES3: J29.2, U4.RES
RX: J2.1, U1.RX
RX1: J7.1, U2.RX
RX2: J18.1, U3.RX
RX3: J26.1, U4.RX
SCL: J1.4, J8.4, J9.4, J10.4, Q2.2, R2.2
SCL1: J3.10, U1.SCL
SCL2: J5.4, J14.4, J15.4, J16.4, Q4.2, R7.2
SCL3: J11.10, U2.SCL
SCL4: J17.4, J22.4, J23.4, J24.4, Q6.2, R11.2
SCL5: J19.10, U3.SCL
SCL6: J25.4, J30.4, J31.4, J32.4, Q8.2, R15.2
SCL7: J27.10, U4.SCL
SDA: J1.3, J8.3, J9.3, J10.3, Q1.2, R3.2
SDA1: J3.9, U1.SDA
SDA2: J5.3, J14.3, J15.3, J16.3, Q3.2, R1.2
SDA3: J11.9, U2.SDA
SDA4: J17.3, J22.3, J23.3, J24.3, Q5.2, R9.2
SDA5: J19.9, U3.SDA
SDA6: J25.3, J30.3, J31.3, J32.3, Q7.2, R13.2
SDA7: J27.9, U4.SDA
TX: J2.2, U1.TX
TX1: J7.2, U2.TX
TX2: J18.2, U3.TX
TX3: J26.2, U4.TX
VIN: J6.7, U1.VIN
VIN1: J13.7, U2.VIN
VIN2: J21.7, U3.VIN
VIN3: J29.7, U4.VIN

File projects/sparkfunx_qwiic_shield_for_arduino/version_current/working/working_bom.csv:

"Id";"Designator";"Footprint";"Quantity";"Designation";"Supplier and ref";
1;"J5,J1,J17,J16,J14,J32,J24,J8,J30,J15,J31,J22,J25,J23,J10,J9";"1X04_1MM_RA";16;"";;;
2;"R4,R13,R15,R2,R3,R5,R9,R11,R14,R1,R16,R10,R7,R6,R8,R12";"0603-RES";16;"4.7K";;;
3;"J20,J12,J28,J4";"1X06_NO_SILK";4;"";;;
4;"U$7,U$1,U$10,U$4";"SPARKX-SMALL";4;"SPARKX-LOGO3";;;
5;"FD4,FD7,FD8,FD3,FD6,FD1,FD5,FD2";"FIDUCIAL-1X2";8;"FIDUCIAL1X2";;;
6;"J11,J27,J19,J3";"1X10_NO_SILK";4;"";;;
7;"U3,U2,U1,U4";"UNO_R3_SHIELD_NOLABELS";4;"ARDUINO UNO";;;
8;"U$3,U$6,U$9,U$12";"QWIIC_BOARD_MOUNT_HOLES";4;"QWIIC_BOARD_OUTLINEH";;;
9;"Q7,Q1,Q5,Q8,Q6,Q3,Q2,Q4";"SOT23-3";8;"200mA/50V";;;
10;"J18,J2,J26,J7";"1X08_NO_SILK";4;"";;;
11;"J21,J6,J13,J29";"1X07_NO_SILK";4;"";;;
12;"U$5,U$11,U$2,U$8";"SPARKX-LARGE";4;"SPARKX-LOGO5";;;
13;"LOGO4,LOGO1,LOGO3,LOGO2";"OSHW-LOGO-MINI";4;"OSHW-LOGOMINI";;;

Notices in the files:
projects/sparkfunx_qwiic_rfid_tag/version_current/working/readme.md:
License: MIT
parts and their libraries:
Released under the Creative Commons Attribution Share-Alike 4.0 License
https://creativecommons.org/licenses/by-sa/4.0
